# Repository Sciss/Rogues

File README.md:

# Rogues

This repository contains code for an ongoing art project.
See [Research Catalogue](https://www.researchcatalogue.net/view/1437680/1437681).

(C)opyright 2021–2022 by Hanns Holger Rutz. All rights reserved. This project is released under the
[GNU Affero General Public License](https://github.comt/Sciss/Rogues/blob/main/LICENSE) v3+ and
comes with absolutely no warranties.
To contact the author, send an e-mail to `contact at sciss.de`.

## building

Builds with sbt against Scala 3. See options: `sbt 'common/run --help'`. E.g.

    sbt 'common/runMain de.sciss.rogues.SteinerChain --margin 0 --radius 240 --full-screen --hide-envelope'

    sbt 'common/runMain de.sciss.rogues.Iris --num-blades 7 --full-screen'

    sbt common/assembly
    java -cp common/Rogues-common.jar de.sciss.rogues.ReceiveSensors --gui

    java -Dsun.java2d.opengl=true -cp common/Rogues-common.jar de.sciss.rogues.SwapRogue --margin 0 --full-screen --center-index 5

To improve Pi 4 performance: `java -Dsun.java2d.opengl=true ...`

## cap test

__OBSOLETE__

pigpio must be installed first: http://abyz.me.uk/rpi/pigpio/download.html

    git clone https://github.com/joan2937/pigpio.git
    cd pigpio
    make
    sudo make install

The in `Rogues`:

    sbt common/assembly
    sudo java -cp common/Rogues-common.jar de.sciss.rogues.CapSense

(yes, I need to get rid of the sudo; thanks pi4j)

## fix wiring-pi

__OBSOLETE__

__Important:__ Wiring-Pi is broken on the Pi 4. The pull up/down resistors cannot be configured.
See https://pi4j.com/1.3/install.html#WiringPi_Native_Library -- one needs to replace the installed versions
with an unofficial one!

    sudo apt remove wiringpi -y
    sudo apt install git-core gcc make
    cd ~/Documents/devel/
    git clone https://github.com/WiringPi/WiringPi --branch master --single-branch wiringpi
    cd wiringpi
    sudo ./build

## installing SuperCollider on the Pi

We build SC 3.10.4:

```
cd ~/Documents/devel
git clone https://github.com/supercollider/supercollider.git

sudo apt install libjack-jackd2-dev libsndfile1-dev libasound2-dev libavahi-client-dev \
libreadline-dev libfftw3-dev libxt-dev libudev-dev libncurses5-dev cmake git qttools5-dev qttools5-dev-tools \
qtdeclarative5-dev libqt5svg5-dev qjackctl

cd supercollider
git checkout -b 3.10.4 Version-3.10.4

git submodule update --init --recursive

mkdir build
cd build

cmake -DCMAKE_BUILD_TYPE=Release -DSUPERNOVA=OFF -DSC_ED=OFF -DSC_EL=OFF -DSC_VIM=ON -DNATIVE=ON -DSC_USE_QTWEBENGINE:BOOL=OFF ..

cmake --build . --config Release --target all -- -j3

sudo cmake --build . --config Release --target install
```

This installs in `/usr/local/bin`. If debian package has been installed, it will override through `/usr/bin`,
to remove use `sudo apt remove supercollider-server` (or `-common` I guess?).

We use `JPverb` thus also need `sc3-plugins`:

```
cd ~/Documents/devel
git clone https://github.com/supercollider/sc3-plugins.git

cd sc3-plugins
git checkout -b 3.10.4 643709850b2f22f68792372aaece5fc6512defc6

git submodule update --init --recursive

mkdir build
cd build

cmake -DSC_PATH=/home/pi/Documents/devel/supercollider/ -SC_PATH=/home/pi/.local/share/SuperCollider ..

cmake --build . --config Release

sudo cmake --build . --config Release --target install

```

## access TTL-to-USB via tinyUSB0 on Linux

To avoid root requirement, add user to dialout group:

    sudo usermod -a -G dialout $USER

Prepare reading, setting speed etc.

    stty -F /dev/ttyUSB0 speed 115200 cs8 -cstopb -parenb -echo

Dump output:

    cat /dev/ttyUSB0

Check if other process accesses the USB:

    lsof /dev/ttyUSB0

Running Python REPL in the terminal:

    screen /dev/ttyACM0 115200

(You may need to `sudo apt install screen`)

To stop `screen`, press `ctrl-a` followed by `k`.

## Pn532 tests

https://www.waveshare.com/wiki/PN532_NFC_HAT

Code:

https://www.waveshare.com/w/upload/6/67/Pn532-nfc-hat-code.7z

To unzip: 

    sudo apt install p7zip-full
    mkdir out
    cd out
    7z x ../Pn532-nfc-hat-code.7z

Set both jumpers L0 and L1 to L(ow), to enable UART. Connect the first four pins
to 3v3 / GND / Rx / Tx. Flip Tx/Rx with respect to the TTL-to-USB adapter.

When connected via UART to USB:

```
pn532 = PN532_UART(debug=False, reset=20, dev='/dev/ttyUSB0')
```

## Install HyperPixel

    git clone https://github.com/pimoroni/hyperpixel2r

    cd hyperpixel2r
    sudo ./install.sh

Needs Raspbian Buster not Bullseye!

## Pis

- 192.168.77.35
- 192.168.77.40
- 192.168.77.45 "eve"

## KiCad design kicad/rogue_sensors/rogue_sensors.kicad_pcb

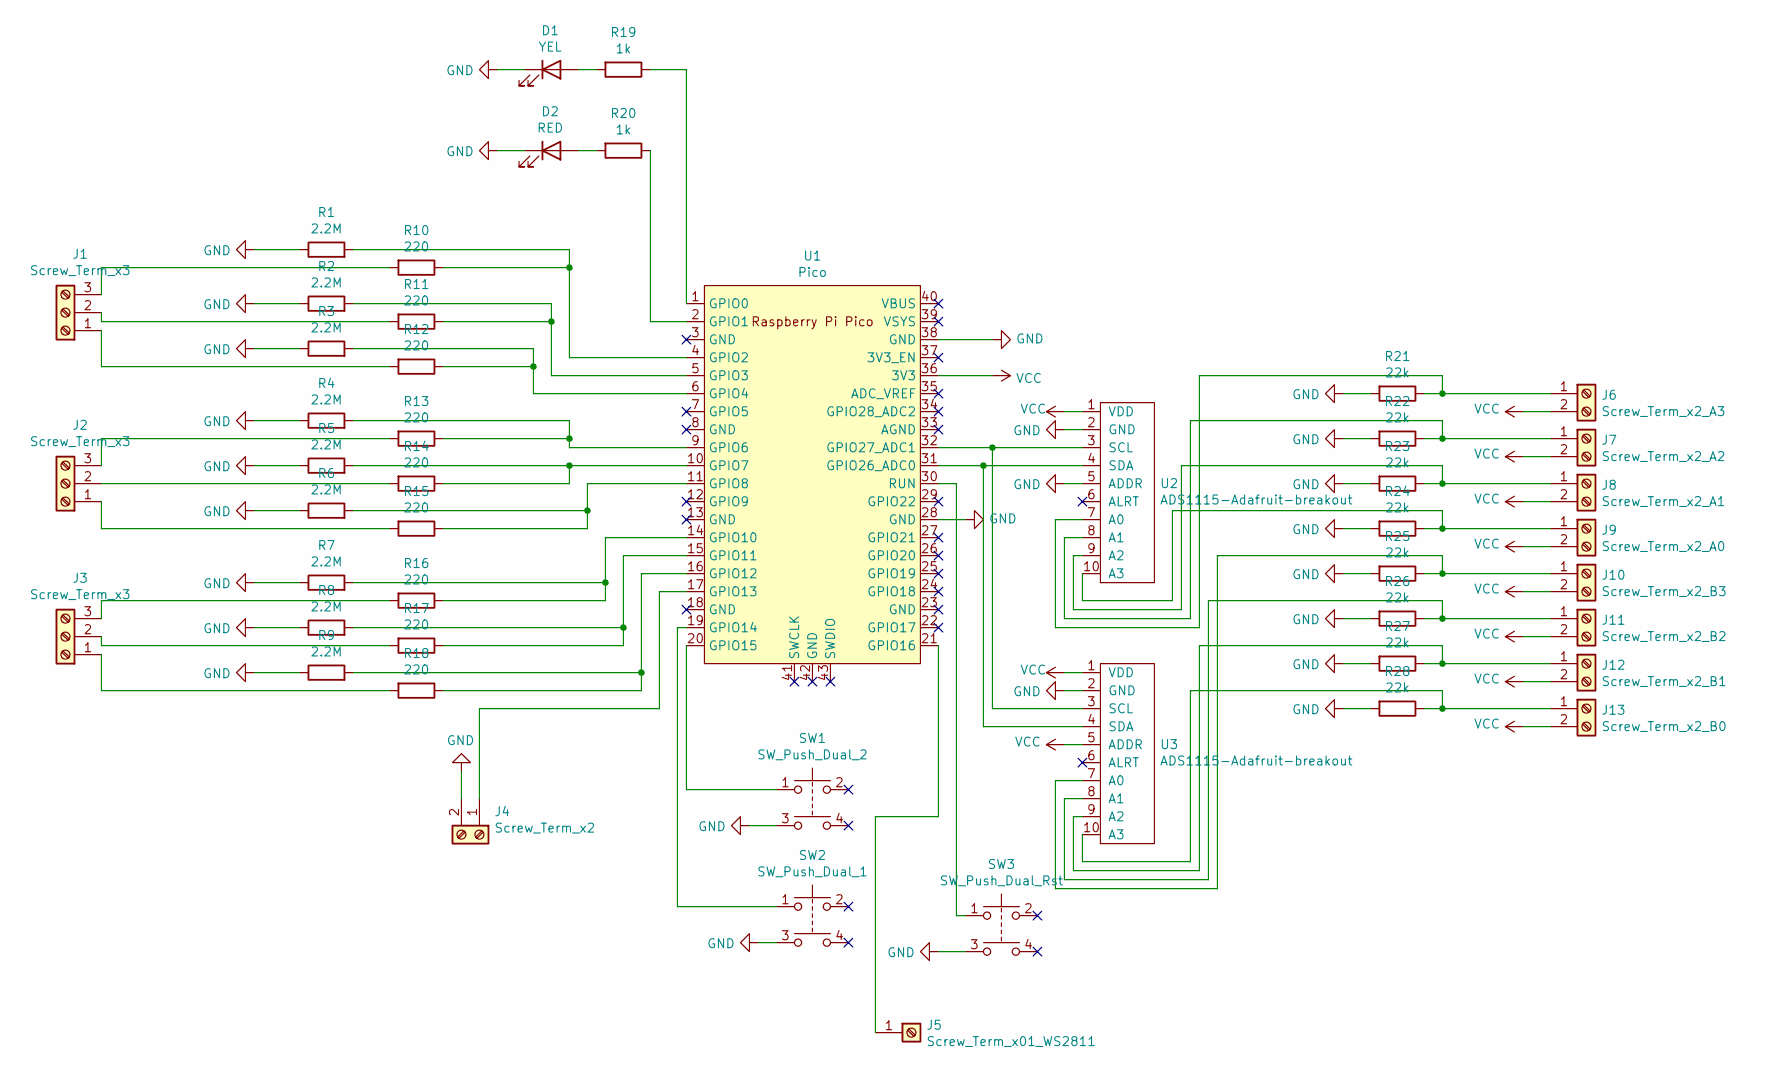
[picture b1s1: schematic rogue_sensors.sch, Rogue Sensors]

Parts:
D1: YEL; LED_D3.0mm
D2: RED; LED_D3.0mm
J1, J2, J3: Screw_Term_x3; TerminalBlock_RND_205-00046_1x03_P5.00mm_Horizontal
J4: Screw_Term_x2; TerminalBlock_RND_205-00045_1x02_P5.00mm_Horizontal
J5: Screw_Term_x01_WS2811; TerminalBlock_MetzConnect_360271_1x01_Horizontal_ScrewM3.0_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
J6: Screw_Term_x2_A3; TerminalBlock_TE_282834-2_1x02_P2.54mm_Horizontal
J7: Screw_Term_x2_A2; TerminalBlock_TE_282834-2_1x02_P2.54mm_Horizontal
J8: Screw_Term_x2_A1; TerminalBlock_TE_282834-2_1x02_P2.54mm_Horizontal
J9: Screw_Term_x2_A0; TerminalBlock_TE_282834-2_1x02_P2.54mm_Horizontal
J10: Screw_Term_x2_B3; TerminalBlock_TE_282834-2_1x02_P2.54mm_Horizontal
J11: Screw_Term_x2_B2; TerminalBlock_TE_282834-2_1x02_P2.54mm_Horizontal
J12: Screw_Term_x2_B1; TerminalBlock_TE_282834-2_1x02_P2.54mm_Horizontal
J13: Screw_Term_x2_B0; TerminalBlock_TE_282834-2_1x02_P2.54mm_Horizontal
R1, R2, R3, R4, R5, R6, R7, R8, R9: 2.2M; R_Axial_DIN0207_L6.3mm_D2.5mm_P7.62mm_Horizontal
R10, R11, R12, R13, R14, R15, R16, R17, R18: 220; R_Axial_DIN0207_L6.3mm_D2.5mm_P7.62mm_Horizontal
R19, R20: 1k; R_Axial_DIN0207_L6.3mm_D2.5mm_P7.62mm_Horizontal
R21, R22, R23, R24, R25, R26, R27, R28: 22k; R_Axial_DIN0207_L6.3mm_D2.5mm_P7.62mm_Horizontal
SW1: SW_Push_Dual_2; Diode_Bridge_DIP-4_W7.62mm_P5.08mm
SW2: SW_Push_Dual_1; Diode_Bridge_DIP-4_W7.62mm_P5.08mm
SW3: SW_Push_Dual_Rst; Diode_Bridge_DIP-4_W7.62mm_P5.08mm
U1: Pico; RPi_Pico_SMD_TH
U2, U3: ADS1115-Adafruit-breakout

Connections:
GND: D1.1 (K), D2.1 (K), J4.2, R1.1, R2.1, R3.1, R4.1, R5.1, R6.1, R7.1, R8.1, R9.1, R21.2, R22.2, R23.2, R24.2, R25.2, R26.2, R27.2, R28.2, SW1.3, SW2.3, SW3.3, U1.28 (GND), U1.38 (GND), U2.2 (GND), U2.5 (ADDR), U3.2 (GND)
unnamed: D1.2 (A), R19.2
unnamed: D2.2 (A), R20.2
unnamed: J1.1, R12.2
unnamed: J1.2, R11.2
unnamed: J1.3, R10.2
unnamed: J2.1, R15.2
unnamed: J2.2, R14.2
unnamed: J2.3, R13.2
unnamed: J3.1, R18.2
unnamed: J3.2, R17.2
unnamed: J3.3, R16.2
unnamed: J4.1, U1.17 (GPIO13)
unnamed: J5.1, U1.21 (GPIO16)
unnamed: J6.1, R21.1, U2.7 (A0)
unnamed: J7.1, R22.1, U2.8 (A1)
unnamed: J8.1, R23.1, U2.9 (A2)
unnamed: J9.1, R24.1, U2.10 (A3)
unnamed: J10.1, R25.1, U3.7 (A0)
unnamed: J11.1, R26.1, U3.8 (A1)
unnamed: J12.1, R27.1, U3.9 (A2)
unnamed: J13.1, R28.1, U3.10 (A3)
unnamed: R1.2, R10.1, U1.4 (GPIO2)
unnamed: R2.2, R11.1, U1.5 (GPIO3)
unnamed: R3.2, R12.1, U1.6 (GPIO4)
unnamed: R4.2, R13.1, U1.9 (GPIO6)
unnamed: R5.2, R14.1, U1.10 (GPIO7)
unnamed: R6.2, R15.1, U1.11 (GPIO8)
unnamed: R7.2, R16.1, U1.14 (GPIO10)
unnamed: R8.2, R17.1, U1.15 (GPIO11)
unnamed: R9.2, R18.1, U1.16 (GPIO12)
unnamed: R19.1, U1.1 (GPIO0)
unnamed: R20.1, U1.2 (GPIO1)
unnamed: SW1.1, U1.20 (GPIO15)
unnamed: SW2.1, U1.19 (GPIO14)
unnamed: SW3.1, U1.30 (RUN)
unnamed: U1.31 (GPIO26_ADC0), U2.4 (SDA), U3.4 (SDA)
unnamed: U1.32 (GPIO27_ADC1), U2.3 (SCL), U3.3 (SCL)
VCC: J6.2, J7.2, J8.2, J9.2, J10.2, J11.2, J12.2, J13.2, U1.36 (3V3), U2.1 (VDD), U3.1 (VDD), U3.5 (ADDR)

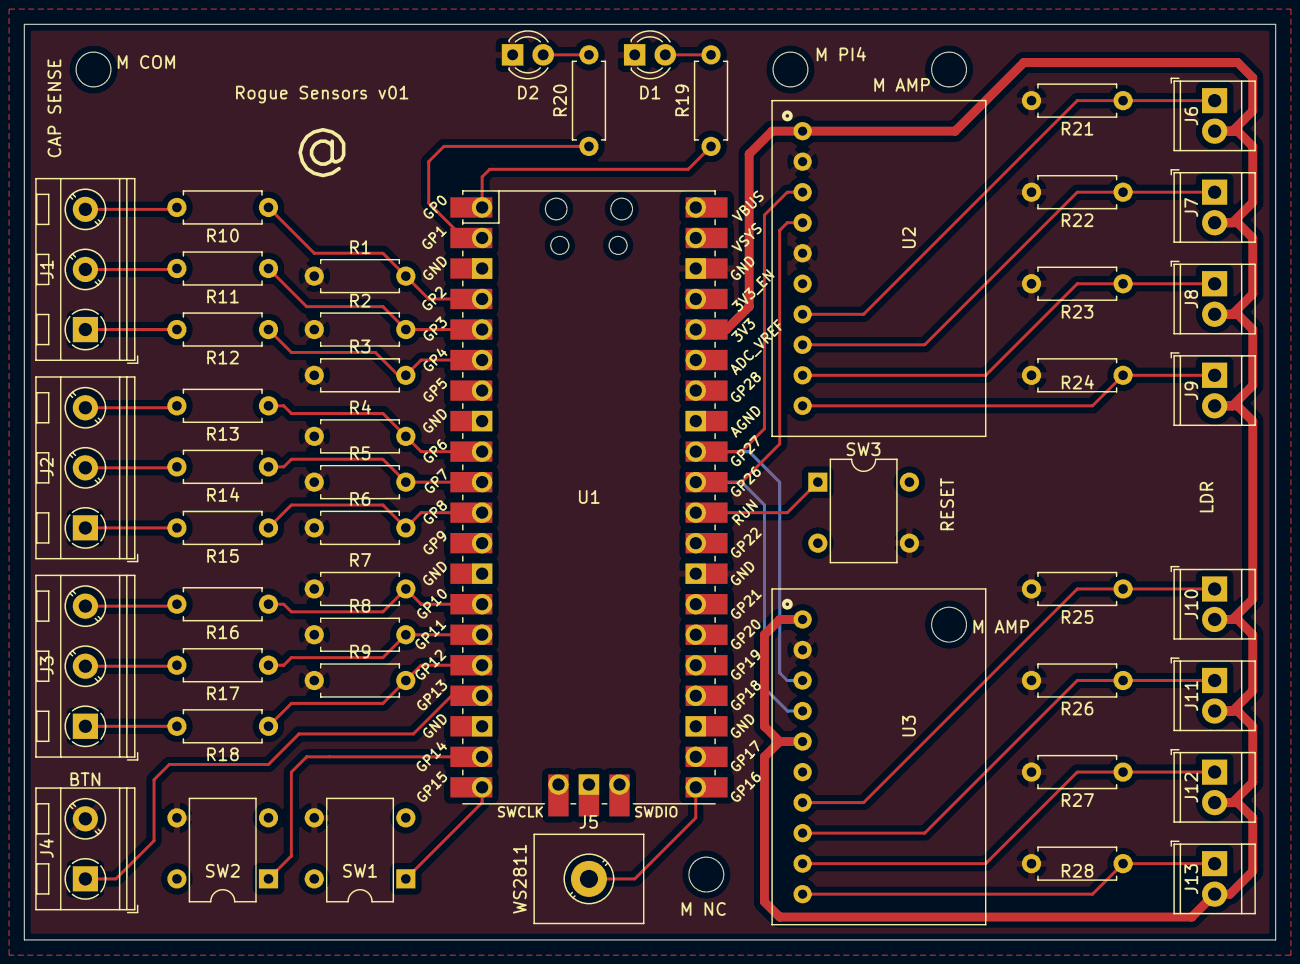
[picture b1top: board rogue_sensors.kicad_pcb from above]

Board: 2 copper layers, 104.1 x 76.2 mm, 49 parts (0 on the bottom side), 39 nets.

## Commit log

2021-12-08 init
2021-12-08 correct speed <>
2021-12-08 try image <>
2021-12-08 try counter rotation and alpha <>
2021-12-08 cli options, ready for pi test, I guess <>
2021-12-08 hide cursor, escape to exit undecorated <>
2021-12-17 start cap test <>
2021-12-17 up sbt <>
2021-12-17 enable sbt-assembly settings <>
2021-12-17 wtf sbt <>
2021-12-17 assembly una mierda <>
2021-12-17 mein gott ist p4j v2 eine sch*** <>
2021-12-19 readme <>
2022-01-05 circuitpython touch example
2022-01-06 binary sensors more or less ok <>
2022-01-07 hid receive tests; hid4java doesn't, purejavahidapi do work on linux <>
2022-01-07 test commit (add codeberg) <>
2022-01-08 six sensors <>
2022-01-10 ads1115 ok <>
2022-01-10 pn532 _detection_ ok via SPI <>
    - haven't tested read/write yet
2022-01-16 soldered Pin layout <>
2022-01-17 ads1115: works with two chips, six sensors <>
2022-01-26 test 3W led <>
2022-01-29 add kicad stuff <>
2022-02-08 off-but-test <>
2022-02-15 first pcb test <>
2022-02-15 both sensors <>
2022-02-15 typo <>
2022-02-15 test with only one resistor <>
2022-02-15 test both buttons <>
2022-02-15 test 'off' button <>
2022-02-15 try pixel <>
2022-02-15 python huh <>
2022-02-15 all chans <>
2022-04-01 notes on Pn532 and Hyperpixel2r <>
2022-04-07 iris test <>
2022-04-07 hmmm <>
2022-04-07 iris ok <>
    - just slow on the pi, but now I'm suspecting Java2D with the
    default JDK package
2022-04-12 add ldr only for pupik <>
2022-04-12 receive ldr text <>
2022-04-12 add i2c_scan <>
2022-04-12 ok, i think was wrong device <>
2022-04-12 do not pad sensor values <>
2022-04-12 is it non-blocking? <>
2022-04-12 ok ? <>
2022-04-12 pfff <>
2022-04-12 ok (on laptop) <>
    - seems one ads was simply bad/broken
2022-04-12 that bloody python3 division <>
2022-04-13 ldr recorder and OSC ok? <>
2022-04-25 try other sync
2022-04-25 scan rota test <>
2022-04-27 begin canvas movement <>
2022-04-27 scripts <>
2022-04-27 history ldr ok <>
2022-04-27 fire a bend <>
2022-04-29 add scan63 <>
    - n.b. fibre63 is place holder

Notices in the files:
kicad/rogue_sensors/rogue_sensors.kicad_pcb:
License: CC BY-NC-SA 4.0
kicad/rogue_sensors/rogue_sensors.sch:
https://creativecommons.org/licenses/by-nc-sa/4.0
